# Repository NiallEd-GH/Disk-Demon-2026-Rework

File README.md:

# Disk-Demon-2026-Rework
A rework of the original 1987 Disk Demon using components available in 2026. 

A couple of years ago I rediscovered my old Commodore 64 setup from the 1980s.

While I was getting it all working again, I noticed that one of the disk drives contained a board with words 'Disk Demon' written on one of the ICs. I was curious to find out more about it.....

It turns out that Disk Demon was a version of Professional DOS. At the time, Disk Demon/Professional DOS claimed to be the fasted floppy disk accelerator for the Commodore 64 in the world !

It was released and sold in the UK by Datel Electronics for the Commodore 1541 disk drive. Unlike Professional DOS, which was available for both the Expansion Port and User Port, Disk Demon was only available for the User Port.

As few people seem to have heard of it, I decided to make this lesser known variant of Professional DOS available again in 2026.

It was important that all the parts should be easy to source and the biggest stumbling block was that the original board used an 82S123, 32x8 Bipolar PROM but blank 82S123 PROMs are difficult to find and also, much harder to program than EPROMs.

As EPROMs are not fast enough to replace the PROM, I looked at a PLD.

Although the Lattice GAL is the one most people have heard of, they are no longer made.

Fortunately, a company called Microchip are still making their version of the 16V8 and 22V10 GALs known as the ATF16V8 and ATF22V10.

I redrew the schematic in Kicad, modified the original design to use an ATF16V8 (& added a few bypass capacitors while I was at it) and created a new PCB.

The board is similar in appearance to the original but it is not identical so I decided to call it 'Disk Demon 2026 Rework'

The board has been tested in several different 1541 disk drives, both ALPS & Newtronics and performs well.

Datel originally claimed that a 202 Block file could be loaded in around 2.5 seconds. I have not been able to reproduce that time with either the original board or this rework. But, I have managed to load 202 blocks in 3.5 seconds which is good enough for me.

I have included a Kicad Schematic for both the original 1987 Disk Demon and the 2026 Rework.

There are also Gerber files for the 'Rework' PCB, along with all the programming information for the ATF16V8, the 256kb Disk Demon EPROM and the C64 Disk Demon Kernal ROM.

For those planning to make their own Disk Demon, there is a step by step assembly guide.

The PCB is available as a Shared Project on PCBWay https://www.pcbway.com/project/shareproject/Disk_Demon_2026_Rework_C64_Rev3a_214e8d53.html

The User Port version of the Professional DOS Kernal ROM for the Commodore 64 is included in case you want to compare it to the Disk Demon C64 Kernal ROM

Datel also sold a 'Disk Demon Utility Disk' so there is a D64 image for that.

I have reproduced the Disk Demon documentation which I suggest reading if you want to get the most from the board.

The most common problem getting the board to work is down to poor connections where the board plugs into the 6502 socket on the 1541 system board. I strongly suggest that you replace the original 40 pin CPU socket on the 1541 system board with a new one.

The same goes for the 6522 VIA socket !

If you have any issues, please raise them in this thread on Lemon64

https://www.lemon64.com/forum/viewtopic.php?p=1106892

Good luck and enjoy super fast Commodore 64 loading and saving

NiallEd (October 2026)

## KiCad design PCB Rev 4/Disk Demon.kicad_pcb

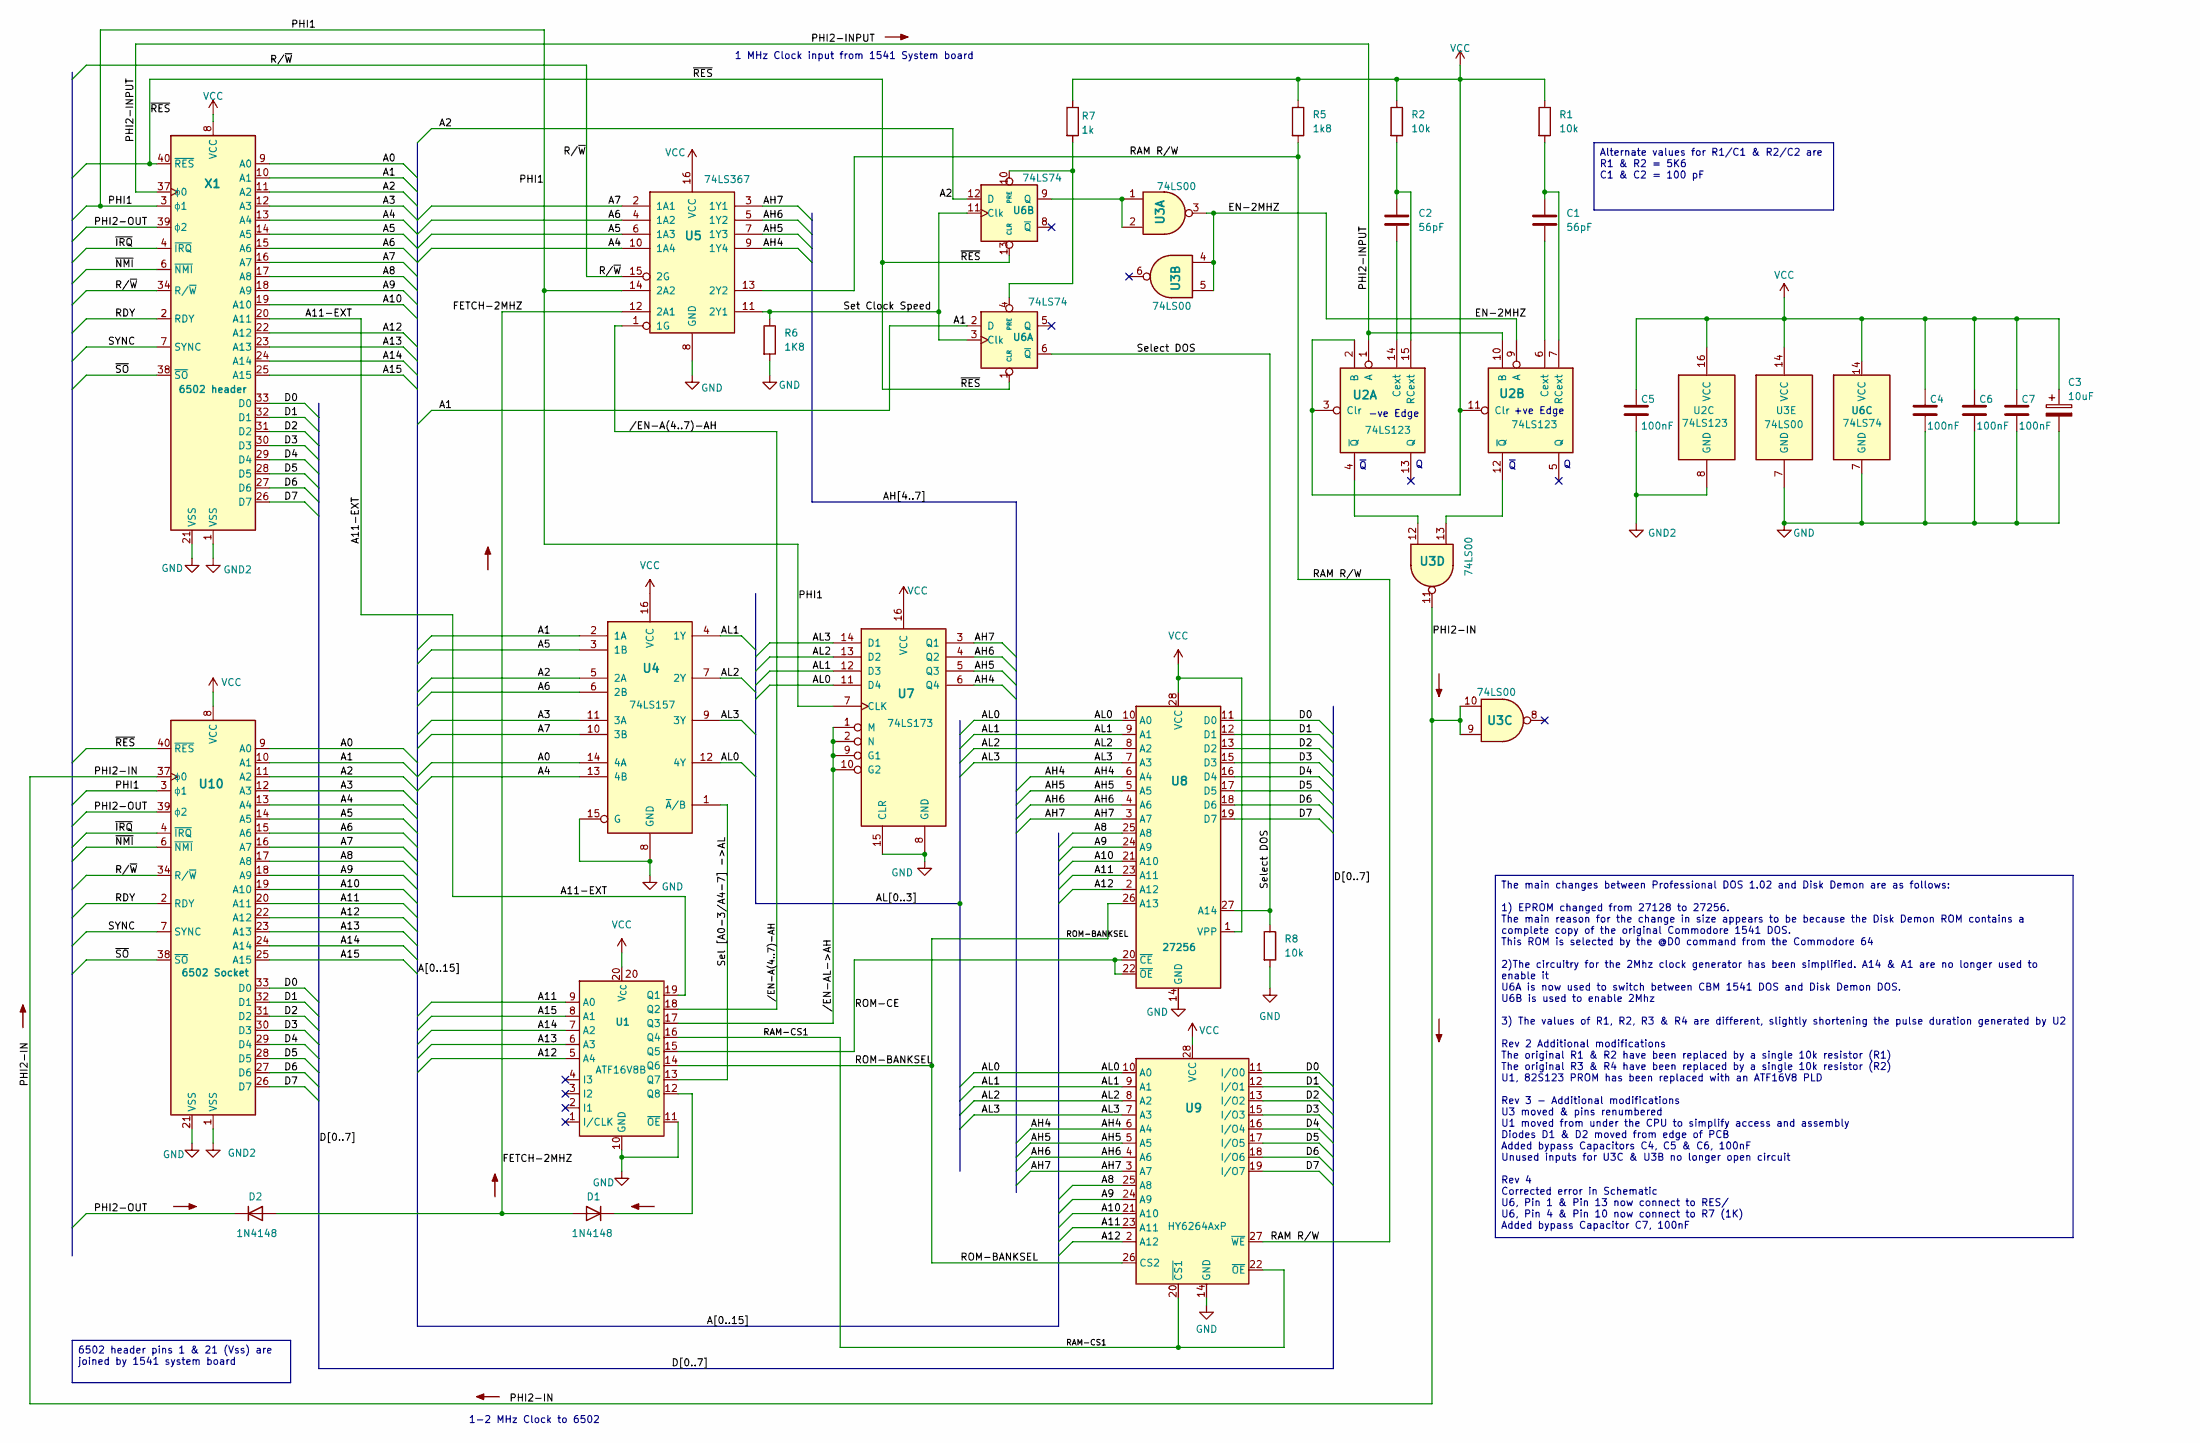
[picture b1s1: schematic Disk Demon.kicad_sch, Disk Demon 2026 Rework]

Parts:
C1, C2: 56pF; R_Axial_DIN0207_L6.3mm_D2.5mm_P2.54mm_Vertical
C3: 10uF; CP_Radial_D4.0mm_P1.50mm
C4, C5, C6, C7: 100nF; C_Disc_D4.7mm_W2.5mm_P5.00mm
D1, D2: 1N4148; D_DO-35_SOD27_P7.62mm_Horizontal
R1, R2: 10k; R_Axial_DIN0207_L6.3mm_D2.5mm_P2.54mm_Vertical
R5: 1k8; R_Axial_DIN0207_L6.3mm_D2.5mm_P7.62mm_Horizontal
R6: 1K8; R_Axial_DIN0207_L6.3mm_D2.5mm_P7.62mm_Horizontal
R7: 1k; R_Axial_DIN0207_L6.3mm_D2.5mm_P7.62mm_Horizontal
R8: 10k; R_Axial_DIN0207_L6.3mm_D2.5mm_P7.62mm_Horizontal
U1: ATF16V8B; DIP-20_W7.62mm
U2: 74LS123; DIP-16_W7.62mm
U3: 74LS00; DIP-14_W7.62mm
U4: 74LS157; DIP-16_W7.62mm
U5: 74LS367; DIP-16_W7.62mm
U6: 74LS74; DIP-14_W7.62mm
U7: 74LS173; DIP-16_W7.62mm
U8: 27256; DIP-28_W15.24mm
U9: HY6264AxP; DIP-28_W15.24mm
U10: 6502 Socket; DIP-40_W15.24mm_Socket
X1: 6502 header; DIP-40_W15.24mm_Socket

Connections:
/A0: U4.14 (4A), U10.9 (A0), X1.9 (A0)
/A1: U4.2 (1A), U6.2 (D), U10.10 (A1), X1.10 (A1)
/A2: U4.5 (2A), U6.12 (D), U10.11 (A2), X1.11 (A2)
/A3: U4.11 (3A), U10.12 (A3), X1.12 (A3)
/A4: U4.13 (4B), U5.10 (1A4), U10.13 (A4), X1.13 (A4)
/A5: U4.3 (1B), U5.6 (1A3), U10.14 (A5), X1.14 (A5)
/A6: U4.6 (2B), U5.4 (1A2), U10.15 (A6), X1.15 (A6)
/A7: U4.10 (3B), U5.2 (1A1), U10.16 (A7), X1.16 (A7)
/A8: U8.25 (A8), U9.25 (A8), U10.17 (A8), X1.17 (A8)
/A9: U8.24 (A9), U9.24 (A9), U10.18 (A9), X1.18 (A9)
/A10: U8.21 (A10), U9.21 (A10), U10.19 (A10), X1.19 (A10)
/A11: U1.9 (A0), U8.23 (A11), U9.23 (A11), U10.20 (A11)
/A11-EXT: U1.19 (Q1), X1.20 (A11)
/A12: U1.5 (A4), U8.2 (A12), U9.2 (A12), U10.22 (A12), X1.22 (A12)
/A13: U1.6 (A3), U10.23 (A13), X1.23 (A13)
/A14: U1.7 (A2), U10.24 (A14), X1.24 (A14)
/A15: U1.8 (A1), U10.25 (A15), X1.25 (A15)
/AH4: U5.9 (1Y4), U7.6 (Q4), U8.6 (A4), U9.6 (A4)
/AH5: U5.7 (1Y3), U7.5 (Q3), U8.5 (A5), U9.5 (A5)
/AH6: U5.5 (1Y2), U7.4 (Q2), U8.4 (A6), U9.4 (A6)
/AH7: U5.3 (1Y1), U7.3 (Q1), U8.3 (A7), U9.3 (A7)
/AL0: U4.12 (4Y), U7.11 (D4), U8.10 (A0), U9.10 (A0)
/AL1: U4.4 (1Y), U7.12 (D3), U8.9 (A1), U9.9 (A1)
/AL2: U4.7 (2Y), U7.13 (D2), U8.8 (A2), U9.8 (A2)
/AL3: U4.9 (3Y), U7.14 (D1), U8.7 (A3), U9.7 (A3)
/D0: U8.11 (D0), U9.11 (I/O0), U10.33 (D0), X1.33 (D0)
/D1: U8.12 (D1), U9.12 (I/O1), U10.32 (D1), X1.32 (D1)
/D2: U8.13 (D2), U9.13 (I/O2), U10.31 (D2), X1.31 (D2)
/D3: U8.15 (D3), U9.15 (I/O3), U10.30 (D3), X1.30 (D3)
/D4: U8.16 (D4), U9.16 (I/O4), U10.29 (D4), X1.29 (D4)
/D5: U8.17 (D5), U9.17 (I/O5), U10.28 (D5), X1.28 (D5)
/D6: U8.18 (D6), U9.18 (I/O6), U10.27 (D6), X1.27 (D6)
/D7: U8.19 (D7), U9.19 (I/O7), U10.26 (D7), X1.26 (D7)
/EN-2MHZ: U2.9 (A), U3.3, U3.4, U3.5
/FETCH-2MHZ: D1.2 (A), D2.2 (A), U5.12 (2A1)
/PHI1: U5.14 (2A2), U7.7 (CLK), U10.3 (ϕ1), X1.3 (ϕ1)
/PHI2-IN: U3.9, U3.10, U3.11, U10.37 (ϕ0)
/PHI2-INPUT: U2.1 (A), U2.10 (B), X1.37 (ϕ0)
/PHI2-OUT: D2.1 (K), U10.39 (ϕ2), X1.39 (ϕ2)
/RAM R/W: R5.2, U5.13 (2Y2), U9.27 (~WE)
/RAM-CS1: U1.16 (Q4), U9.20 (~CS1), U9.22 (~OE)
/RDY: U10.2 (RDY), X1.2 (RDY)
/ROM-BANKSEL: U1.14 (Q6), U8.26 (A13), U9.26 (CS2)
/ROM-CE: U1.15 (Q5), U8.20 (~CE), U8.22 (~OE)
/R/~W: U5.15 (2G), U10.34 (R/~W), X1.34 (R/~W)
/SYNC: U10.7 (SYNC), X1.7 (SYNC)
/Sel [A0-3/A4-7] ->AL: U1.13 (Q7), U4.1 (~A/B)
/Select DOS: R8.1, U6.6 (~Q), U8.27 (A14)
/Set Clock Speed: R6.1, U5.11 (2Y1), U6.3 (Clk), U6.11 (Clk)
//EN-A(4..7)-AH: U1.18 (Q2), U5.1 (1G)
//EN-AL->AH: U1.17 (Q3), U7.1 (M), U7.2 (N), U7.9 (G1), U7.10 (G2)
/~IRQ: U10.4 (~IRQ), X1.4 (~IRQ)
/~NMI: U10.6 (~NMI), X1.6 (~NMI)
/~RES: U6.1 (CLR), U6.13 (CLR), U10.40 (~RES), X1.40 (~RES)
/~SO: U10.38 (~SO), X1.38 (~SO)
GND: C3.2, C4.2, C6.2, C7.2, R6.2, R8.2, U1.10 (GND), U1.11 (~OE), U3.7 (GND), U4.8 (GND), U4.15 (G), U5.8 (GND), U6.7 (GND), U7.8 (GND), U7.15 (CLR), U8.14 (GND), U9.14 (GND), U10.21 (VSS), X1.21 (VSS); also elsewhere on the board
GND2: C5.2, U2.8 (GND), U10.1 (VSS), X1.1 (VSS)
unnamed: D1.1 (K), U1.12 (Q8)
unnamed: C2.2, U2.14 (Cext)
unnamed: C2.1, R2.2, U2.15 (RCext)
unnamed: U2.4 (~Q), U3.12
unnamed: C1.2, U2.6 (Cext)
unnamed: C1.1, R1.2, U2.7 (RCext)
unnamed: U2.12 (~Q), U3.13
unnamed: R7.2, U6.4 (PRE), U6.10 (PRE)
unnamed: U3.1, U3.2, U6.9 (Q)
VCC: C3.1, C4.1, C5.1, C6.1, C7.1, R1.1, R2.1, R5.1, R7.1, U1.20 (V_{CC}), U2.2 (B), U2.3 (Clr), U2.11 (Clr), U2.16 (VCC), U3.14 (VCC), U4.16 (VCC), U5.16 (VCC), U6.14 (VCC), U7.16 (VCC), U8.1 (VPP), U8.28 (VCC), U9.28 (VCC), U10.8 (VCC), X1.8 (VCC)

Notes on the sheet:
1 MHz Clock input from 1541 System board
-ve Edge
1-2 MHz Clock to 6502
+ve Edge
~{Q}
Alternate values for R1/C1 & R2/C2 are R1 & R2 = 5K6 C1 & C2 = 100 pF
6502 header pins 1 & 21 (Vss) are joined by 1541 system board
The main changes between Professional DOS 1.02 and Disk Demon are as follows: 1) EPROM changed from 27128 to 27256. The main reason for the change in size appears to be because the Disk Demon ROM contains a complete copy of the original Commodore 1541 DOS. This ROM is selected by the @D0 command fr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

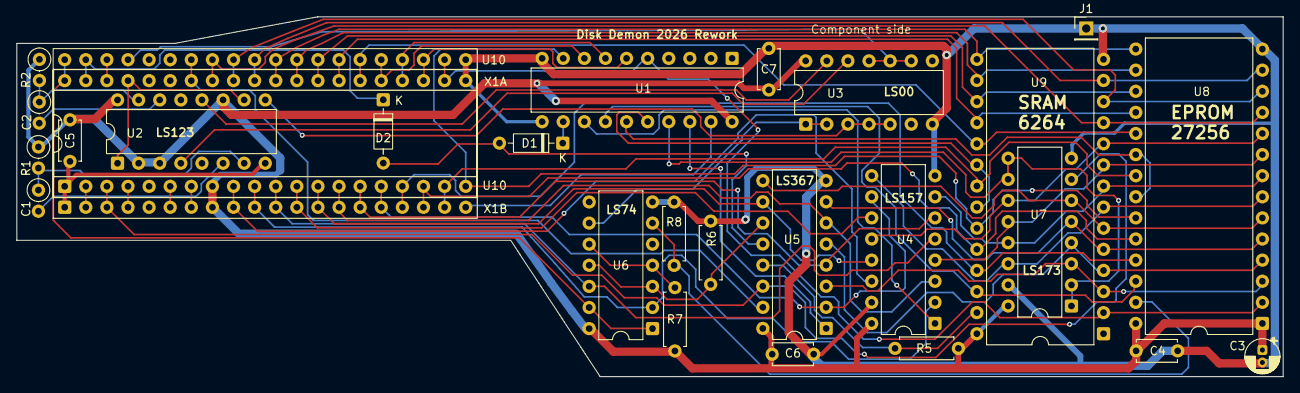
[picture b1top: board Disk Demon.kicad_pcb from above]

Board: 2 copper layers, 152.4 x 43.3 mm, 27 parts (0 on the bottom side), 67 nets.

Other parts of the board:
J1: GND for scope; PinHeader_1x01_P2.54mm_Vertical

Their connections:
GND: J1.1 (Pin_1_1); also elsewhere on the board

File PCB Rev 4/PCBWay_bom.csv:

Designator,Quantity,Value,Footprint,Package,MPN,DNP,Mount_Type,Description,KiLib_Generator,Sim.Device,Sim.Pins
"C1, C2",2,56pF,R_Axial_DIN0207_L6.3mm_D2.5mm_P2.54mm_Vertical,,,,tht,Unpolarized capacitor,resistor/THT,,
C3,1,10uF,CP_Radial_D4.0mm_P1.50mm,,,,tht,Polarized capacitor,capacitor/THT/other,,
"C4, C5, C6, C7",4,100nF,C_Disc_D4.7mm_W2.5mm_P5.00mm,,,,tht,Unpolarized capacitor,capacitor/THT/other,,
"D1, D2",2,1N4148,D_DO-35_SOD27_P7.62mm_Horizontal,,,,tht,"100V 0.15A standard switching diode, DO-35",diode/THT,D,1=K 2=A
J1,1,GND for scope,PinHeader_1x01_P2.54mm_Vertical,,,,tht,"Generic connector, single row, 01x01, script generated (kicad-library-utils/schlib/autogen/connector/)",connector/pin_header_socket,,
"R1, R2",2,10k,R_Axial_DIN0207_L6.3mm_D2.5mm_P2.54mm_Vertical,,,,tht,Resistor,resistor/THT,,
R5,1,1k8,R_Axial_DIN0207_L6.3mm_D2.5mm_P7.62mm_Horizontal,,,,tht,Resistor,resistor/THT,,
R6,1,1K8,R_Axial_DIN0207_L6.3mm_D2.5mm_P7.62mm_Horizontal,,,,tht,Resistor,resistor/THT,,
R7,1,1k,R_Axial_DIN0207_L6.3mm_D2.5mm_P7.62mm_Horizontal,,,,tht,Resistor,resistor/THT,,
R8,1,10k,R_Axial_DIN0207_L6.3mm_D2.5mm_P7.62mm_Horizontal,,,,tht,Resistor,resistor/THT,,
U1,1,ATF16V8B,DIP-20_W7.62mm,,,,tht,"High-performance EE PLD, PAL Device Emulation / PAL Replacement, DIP-20",package/DIP/legacy,,
U10,1,6502 Socket,DIP-40_W15.24mm_Socket,,,,tht,"8-bit NMOS Microprocessor, 64K, DIP-40",package/DIP/legacy,,
U2,1,74LS123,DIP-16_W7.62mm,,,,tht,Dual retriggerable Monostable,package/DIP/legacy,,
U3,1,74LS00,DIP-14_W7.62mm,,,,tht,quad 2-input NAND gate,package/DIP/legacy,,
U4,1,74LS157,DIP-16_W7.62mm,,,,tht,Quad 2 to 1 line Multiplexer,package/DIP/legacy,,
U5,1,74LS367,DIP-16_W7.62mm,,,,tht,Hex Bus Driver 3-state outputs,package/DIP/legacy,,
U6,1,74LS74,DIP-14_W7.62mm,,,,tht,"Dual D Flip-flop, Set & Reset",package/DIP/legacy,,
U7,1,74LS173,DIP-16_W7.62mm,,,,tht,"4-bit D-type Register, 3 state out",package/DIP/legacy,,
U8,1,27256,DIP-28_W15.24mm,,,,tht,"UV Erasable EPROM 128 KiBit, [Obsolete 2000-11]",package/DIP/legacy,,
U9,1,HY6264AxP,DIP-28_W15.24mm,,,,tht,"Not in Production, 8Kx8 bit Static RAM, 70/85/100/120/150ns, DIP-28",package/DIP/legacy,,
X1,1,6502 header,DIP-40_W15.24mm_Socket,,,,tht,"8-bit NMOS Microprocessor, 64K, DIP-40",package/DIP/legacy,,
